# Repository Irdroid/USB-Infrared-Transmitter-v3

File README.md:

# Irdroid USB Infrared Transmitter v3

The Irdroid USB Infrared transmitter device provides infrared remote control capabilities for the host computer. It is supported in Linux , MS Windows and Android. It is capable of controlling appliances such as TVs, STBs, Air Conditioners and basically any device that is controlled via infrared signals.
### Motivation
The first revisions of the Irdroid USB Infrared Transmitter product used Microchip's PIC18F2550 MCU.The increasing cost of this MCU and the limited availability of the MCU, after Covid/2020, demanded the commencement of this project.

### The search for a replacement MCU
During the development of this code a single piece of PIC18F2550 cost around 8USD. So hell-yeah that was a huge motivator.
The search for alternative microcontroller took place years before this project, but no viable candidate was found, until now. The requirements were met by a MCU manufactured by a Chineese company called WCH, and the selected MCU was CH552, a Harward architecture 89c51 core, with all the required peripherals. 
Last but not least, one pcs of the CH552 MCU costs 0.25 USD, providing similar features and performance, so voila...

### The Idea
- Design and implement a USB infrared transmitter adapter, that would be a drop-in replacement for the legacy Irdroid USB Infrared transmitter, without any re-design or re-work to the host drivers. With other words, we had to design and implement the firmware in such way, that the host could't differentiate the legacy and the new device. That turned out to be a challenging task. 
- Design and manufacture a printed circuit board for the new MCU, that would fit into the legacy enclosure, which would further reduce end product cost.
- Take care of the possibility for automatic flashing , during manufacture.
### The Challenges

- Significant differences between the two MCUs in terms of possibilities to configure the system clocks and clock dividers for the timer modules and the PWM module.
    - The Microchip's PIC18f2550, provides greater range of frequency division factors and it is a bit flexible in comparison with the WCH CH55x family of MCUs especially for the PWM module clock configuration.
    - There was a necessity to postprocess the IR data comming from the host to the WCH 552 MCU in order to re-align with its timer configuration for sending the RAW IR data
- Differences in the USB controller in both MCUs. Tweaking in software was required.
    - The implementation on the PIC18F2550 was done using polling the USB controller, rather than using interrupts.
    - The implementation on the CH552 was done using interrupts.
- Different development environment, no debugging capabilities
    - Microchip's PIC18F2550 has debugging support using a Pickit3 ICD adapter
    - The CH55x microcontrollers dont have hardware debugging support, thus in our case debugging was done with redirected printf on a small LCD screen. This is very innacurate in comparison with a hardware debugging support.
- Differences in flashing the firmware to the MCUs
    - The Microchip's PIC18F2550 uses PickIt 3 flash fromgrammers for flashing, they dont come with a bootloader, but pickit3 programmers has a very useful feature for in-field programming - no host required.
    - The WCH CH55x comes with a built in bootloader, which allows for flashing via USB or Serial interface.

### Software Development 

In terms of software, the idea was to re-use the code from the Irdroid USB Infrared Transmitter, which was written in C and port it to the new architecture. CH55x MCUs have a SDK with the SDCC compiler and it can be used with Visual Studio Code, which was our choise for the IDE. 

    - For this MCU there are no debugging capabilities, so we have connected an small i2c OLED display for brief debugging messages with printf.
    - The Saleae Logic analyzer was used also as a tool for debugging and measuring the IR signal output.

### Hardware Design

Due to the fact that we wanted to re-use the already available enclosure, which is used for the previous versions of the Irdroid USB Infrared Transmitter, we have designed the PCB with the same layout and size in order to fit the existing enclosure. For the design of the schematics and the pcb layout we have used EagleCad. A two sides single layer design with FR4 material. The newly designed adapter practically uses almost the same components as in the previous version, and even looks very similar 3 IR LEDs , same enclosure, same USB connector.

### CH552 Hardware
The MCU is 8-bit Harvard architecture 89c51 CPU, 256 bytes of fast RAM and a bit more
than 1k of slower xRam, 3 timer modules, 2 PWM modules, dataflash of 128 Bytes and a hardware USB 2.0 controller.
The above features and its price made it the perfect candidate for the project.

## CH552 SDK
The MCU could be programmed in C and it comes with a SDK (with some examples) for the SDCC compiler. The build system used is GNU Make.

## PURCHASE a SAMPLE UNIT
If you want to support us or you are interested in the product, purchase assembled and tested unit by clicking on the link below:
[Purchase a sample from Irdroid](https://irdroid.eu/product/usb-infrared-transmitter/)

Or purchase from Tindie:
[Purchase a sample from Tindie](https://www.tindie.com/products/irdroid/usb-infrared-transmitter-v3/)

## Instructions for usage of the code

    - Install the SDCC compiler on Linux - apt install sdcc
    - Install vscode and C/C++ plugins and Makefiles plugin for vscode
    - Clone this repository
    - Open a terminal , cd into the source code directory and type code .
    - When vscode loads open a terminal and type "make all", to compile the project
    - In order to flash the binary to the MCU , make sure the ch552 unit is in bootloader mode and type "make flash" in the terminal
    - To clean the project type "make clean"

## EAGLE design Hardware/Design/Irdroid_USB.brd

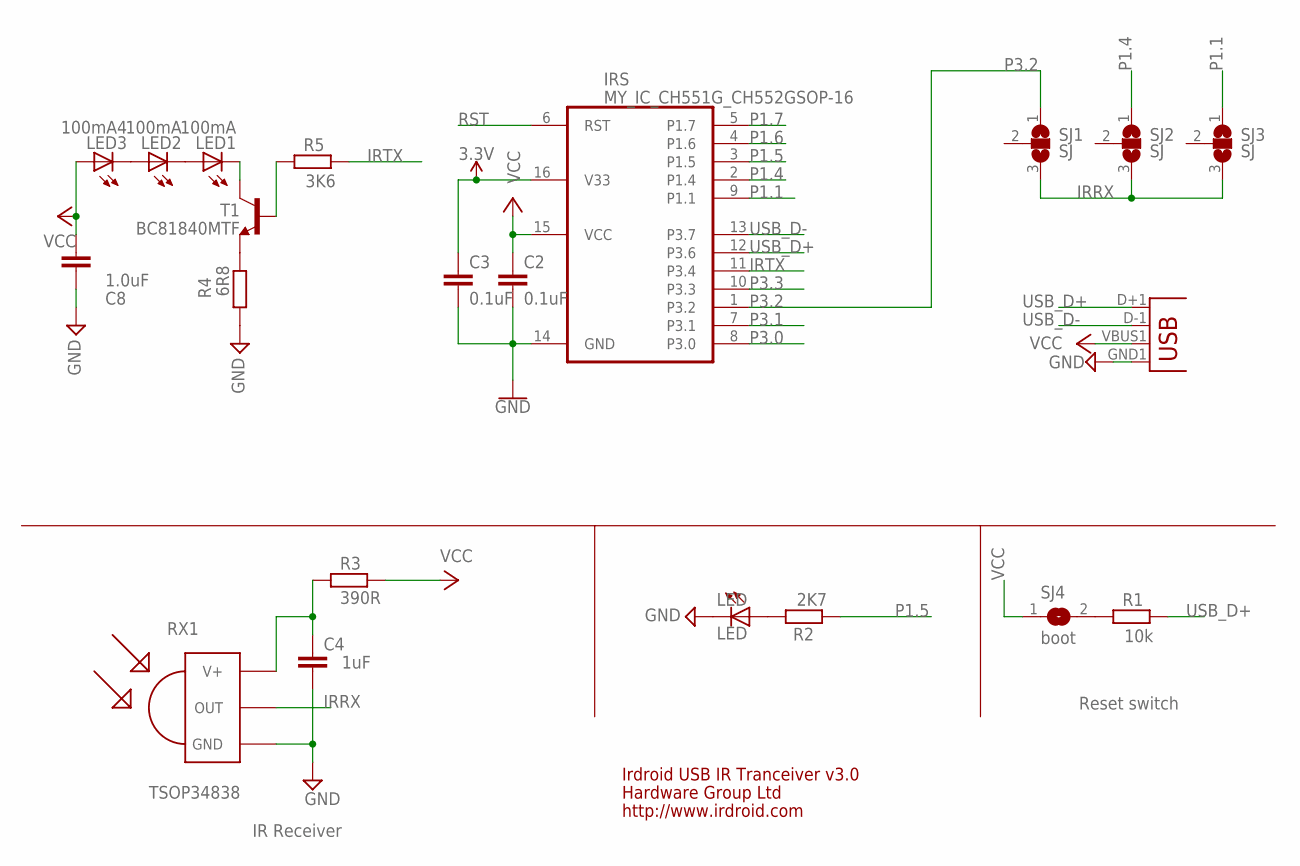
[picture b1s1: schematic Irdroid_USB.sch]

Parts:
C2, C3: 0.1uF; C0805K; LCSC C16834
C4: 1uF; C603
C8: 1.0uF; C603
IRS: MY_IC_CH551G_CH552GSOP-16; MY_IC_SO16; LCSC C111292
JP2: USBA-SMD-MALE; USB-A-SMT-MALE
LED: LED; CHIP-LED0805
LED1, LED2: 100mA; LED3MM
LED3: 100mA4; LED3MM
R1: 10k; R603
R2: 2K7; R603
R3: 390R; R603
R4: 6R8; M1206
R5: 3K6; R603
RX: TSOP34838; TSOP18XX
SJ1, SJ2, SJ3: SJ; SJ_2
SJ4: boot; SJ
T1: BC81840MTF; SOT23-BEC

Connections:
3.3V: C3.1, IRS.16 (V33)
GND: C2.2, C3.2, C4.2, C8.2, IRS.14 (GND), JP2.GND1 (GND), LED.C, R4.1, RX.GND
IRRX: RX.OUT, SJ1.3, SJ2.3, SJ3.3
IRTX: IRS.11 (P3.4), R5.2
unnamed: R1.1, SJ4.2
unnamed: LED1.A, LED2.K (C)
unnamed: LED2.A, LED3.K (C)
unnamed: R4.2, T1.E
unnamed: LED.A, R2.1
unnamed: C4.1, R3.1, RX.VCC (V+)
unnamed: R5.1, T1.B
unnamed: LED1.K (C), T1.C
P1.1: IRS.9 (P1.1), SJ3.1
P1.4: IRS.2 (P1.4), SJ2.1
P1.5: IRS.3 (P1.5), R2.2
P1.6: IRS.4 (P1.6)
P1.7: IRS.5 (P1.7)
P3.0: IRS.8 (P3.0)
P3.1: IRS.7 (P3.1)
P3.2: IRS.1 (P3.2), SJ1.1
P3.3: IRS.10 (P3.3)
RST: IRS.6 (RST)
USB_D+: IRS.12 (P3.6), JP2.D+1 (D+), R1.2
USB_D-: IRS.13 (P3.7), JP2.D-1 (D-)
VCC: C2.1, C8.1, IRS.15 (VCC), JP2.VBUS1 (VBUS), LED3.A, R3.2, SJ4.1

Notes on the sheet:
RX1
TSOP34838
Reset switch
IR Receiver
Hardware Group Ltd
Irdroid USB IR Tranceiver v3.0
http://www.irdroid.com

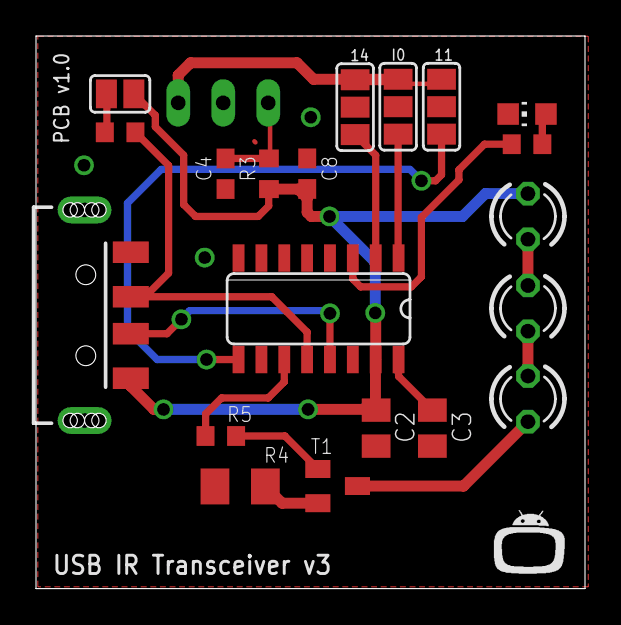
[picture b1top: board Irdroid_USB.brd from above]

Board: 2 copper layers, 30.5 x 30.7 mm, 21 parts (1 on the bottom side), 19 nets.

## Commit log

2025-01-22 fixed align_irtoy_ch552 function
2025-01-28 Added irs.c which will hold the sampling code, added the state machine in main
2025-01-28 Added irtoy struct to xdata
2025-01-31 Working Transmit mode with CH552; Irdroid USB v3.0 on its way!
2025-02-02 Applied some formatting for function declarations
2025-02-02 Updated device descriptors
2025-02-02 Added debug functionality, #DEBUG is defined in config.h
2025-02-03 Added debugging switch in Makefile
2025-02-03 Description about the available debugging options
2025-02-04 Moved the debugging functionality into the ir service C file
2025-02-04 renamed back ir service
2025-02-04 Updated irtoy version function
2025-02-06 Revised debugging, add dataflash eeprom support
2025-02-06 updated debugging
2025-02-06 Added hardware version
2025-02-07 Switched to a 2MHz timer clock
2025-02-08 Timer 0 const is 43 0.000021333/(1/(FCPU/12))
2025-02-09 Test INT0 and timer0 for IR rx , use the CDC to send the data to the host
2025-02-10 timer_val was not calculated correctly , error with bitwise operations
2025-02-15 IR receiver test with Timer2 and P14 in capture mode
2025-02-15 IR reception and measurement using TO and T2
2025-02-16 Added uint16_t division routines
2025-02-16 added rxflag1 and rxflag2 to avoid overflows
2025-02-16 Added description to rxflag1 and rxflag2
2025-02-16 Added configuration for the IRRX pin
2025-02-21 fixed a bug in int0 routine
2025-02-22 Fixed PWM frequency divider , wrong frequency
2025-02-22 IR RX working, abled to sample with the received signal
2025-02-22 Added Pwm_Configure function, part of the Soft PWM functionality
2025-02-23 Fixed a bug with zeroing CDC In buffer in the timer0 interrupt routine
2025-02-24 Added soft pwm functionality using timer 1; TODO: test the solution
2025-02-24 First tests with the Soft PWM implementation fixed the timer1 calculation formula and added a drift constant
2025-02-25 Soft PWM functionality tested. working!
2025-02-25 Fixed the blocking CDC read in irs.c, this is needed if we want to support reception at the same time
2025-02-26 Irdroid USB Infrared Transmitter with hardware and software PWM
2025-03-05 Ledoff on power-up, PWM pin low on boot
2025-03-05 Led off upon enumeration
2025-03-06 Fixed the locking issue, that occur when winlirc exits, the unit remains in sampling mode and if winlirc is started again in locks
2025-03-08 Release FW version 3.2.0
2025-03-08 Updated version in Serial STR; updated pid/ Irdroid pid is 0xf58b
2025-03-22 Fixed the failed to send START TX command in Linux, optimised the ir sampling routine; fixed stability issues; regression tests ongoing
2025-04-16 TRXv3 double buffering transmiter
2025-04-22 USB Infrared transmitter v3.0 double buffering, stable passed 72 hour system tests and performance tests
2025-04-23 Fixed initial enumeration issues in Linux
2025-07-14 Irdroid USB Infrared transmitter is now open source software and hardware
2025-07-14 Update README.md
    Added a picture in readme.md
2025-07-14 Update README.md
    update Readme.md
2025-07-14 Delete Software
    delete the symbolic link
2025-07-14 Create LICENSE
    Added license
2025-07-14 Update README.md
    Revised Readme.md
2025-07-18 Added two pictures with oshw logo
2025-07-18 Update README.md
    changed main image
2025-07-18 Added shipping labels design
2025-10-10 Added firmware update feature(now every irdroid usb infrared transmitter can be flashed using make flash, even when provisioned), Carrier frequency configure feature
2026-01-22 Reception initial implementation
2026-01-22 Switched to fast timer0/2 for testing
2026-02-11 Implemented IR Reception
    Implemented GAP measurement and reporting
    Tested with Winlirc
    Tested Transmission and Reception with WinLirc
    Code formatting, fix ConfigTimer1 function
    updated version
2026-02-27 Fixed a bug, related to the configuration of the SoftPWM carrier frequency
2026-03-13 Added background automated flashing via the Irdroid flashing and testing tools

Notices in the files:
parts and their libraries:
SparkFun-Connectors: Licensing: CC v3.0 Share-Alike You are welcome to use this library for commercial purposes.
SparkFun-PowerSymbols: Licensing: Creative Commons ShareAlike 4.0 International - https://creativecommons.org/licenses/by-sa/4.0
